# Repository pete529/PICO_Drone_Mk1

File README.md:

# PICO Drone Mk1 – Small Quadcopter 

**Status:** ✅ Hardware design complete and ATO builds are green. BOM is populated (see `hardware/build/builds/default/default.bom.csv`). All hardware has been procured and is ready for PCB assembly.

> **New:** Complete user stories and GitHub issue management system available. See [GitHub Issues Creation](#github-issues-creation) below.

## Overview
This project is a complete Raspberry Pi Pico 2W based quadcopter featuring:
- **Raspberry Pi Pico 2W** module (Wi-Fi enabled RP2040 with wireless connectivity)
- **Dual DRV8833** motor driver ICs (4 independent brushed motor outputs)  
- **GY-91 9-DOF IMU** (ICM-20948 + BMP280 for orientation, acceleration, and altitude)
- **Power management** with LiPo Amigo Pro (boost converter + charging circuit)
- **Status LEDs** (power indicator and user-controllable status)
- **User controls** (power button and mode switching)
- **Robust design** with proper power filtering and protection circuits
- **An Android application** that arms and controls the drone via UDP packets

## Project Structure
```
├── hardware/                    # Main atopile project directory
│   ├── main.ato                # Top-level quadcopter module with complete wiring
│   ├── ato.yaml                # Build configuration with multiple targets
│   ├── atopile/components/     # Custom component definitions
│   ├── layouts/                # KiCad PCB layouts (default + test targets)
│   ├── build/                  # Generated build artifacts
│   └── PART_PICKING_GUIDE.md   # Troubleshooting and part selection guide
├── firmware/                    # Drone firmware & shared protocol utils
│   ├── shared/
│   │   └── control_protocol.py  # CSV parser, deadzone/expo, failsafe smoother
│   └── pico/
│       ├── udp_server.py        # Pico W MicroPython UDP server (AP + UDP control)
│       └── drv8833_stub.py      # DRV8833 test mixer/PWM stub for bring‑up
├── android/                     # Android sender app (Compose)
│   ├── app/src/main/
│   │   ├── AndroidManifest.xml
│   │   └── java/com/petedrone/udpsender/MainActivity.kt
│   ├── app/build.gradle.kts
│   ├── settings.gradle.kts
│   ├── build.gradle.kts
│   └── gradle/wrapper/gradle-wrapper.properties
├── user_stories.md             # Complete user stories (6 epics, 25+ features)
├── create_github_issues.ps1    # Script to create GitHub issues from user stories
├── create_issues.bat           # Windows batch file for easy execution
├── GITHUB_ISSUES_README.md     # Documentation for issue management system
└── .github/workflows/          # CI/CD automation
```

## Current Status

### ✅ **Hardware Design Complete**
- **PCB Design**: Complete atopile design with comprehensive component wiring
- **Build System**: Successfully builds with `ato build` - all stages complete
- **Component Integration**: Pico 2W, dual DRV8833s, GY-91 IMU, power management
- **Signal Routing**: All motor control, I2C, power, and user interface connections
- **Build Artifacts**: KiCad files, BOMs, netlists, and manufacturing files generated

### ✅ **Development Infrastructure**  
- **CI/CD**: Automated builds on every commit with artifact publishing
- **Version Management**: Semantic versioning with automated version bumping
- **Issue Management**: Complete user story system with GitHub issue creation
- **Documentation**: Comprehensive guides for building, troubleshooting, and development

### 🔄 **Next Steps**
- **PCB Assembly**: Assemble the procured components onto the PCB
- **Board Bring-up**: Power-on checks, I²C/UART comms, sensor and motor driver validation
- **Firmware Development**: Flight control algorithms and wireless interface
- **Testing & Validation**: Bench tests and initial flight validation

## Build System

### Local Development
Requirements: Python 3.13+, Atopile 0.12.4

```powershell
# Install atopile (Windows-friendly) - Requires Python 3.13 or later
py -m pip install --upgrade atopile==0.12.4

# From repo root, verify and open the design viewer
ato --version
ato view                    # opens default build (App)

# Build the project (generates KiCad files, BOM, netlist)
ato build

# Build a specific target (pickable resistor demo)
ato build --build test_pickable
```

**Build Output:**
- `build/builds/default/` - Main quadcopter design files
- `build/builds/test_pickable/` - Component testing files
- KiCad PCB files (.kicad_pcb)
- Bill of Materials (.bom.csv) 
- Netlists and component reports

Note: The populated BOM is available at `hardware/build/builds/default/default.bom.csv` after a successful build.

### Troubleshooting Build Issues

**VS Code Extension Error: "Client is not running and can't be stopped"**
- **Cause:** Atopile 0.12.4 requires Python 3.13 or later
- **Solution:** 
  1. Install Python 3.13+ from [python.org](https://www.python.org/downloads/)
  2. Reinstall atopile: `py -m pip install --upgrade atopile==0.12.4`
  3. Restart VS Code
  4. Verify with: `python --version` (should show 3.13.0 or higher)

**Build fails with "No such option: --no-color"**
- **Cause:** Option was added in atopile 0.12.x
- **Solution:** Update to atopile 0.12.4: `pip install --upgrade atopile==0.12.4`

**Version compatibility issues**
- This project requires atopile 0.12.4 specifically due to dependency requirements
- Do not downgrade to 0.2.x versions as they use incompatible syntax and features

## Drone control over Wi‑Fi UDP

This repo includes a MicroPython UDP server for Pico W and an Android sender app.

### Pico W (MicroPython) UDP server

Files:
- `firmware/pico/udp_server.py`
- Shared helpers in `firmware/shared/control_protocol.py`

Behavior:
- Starts Wi‑Fi AP: SSID `PicoDrone`, password `drone1234`
- Listens on UDP port 8888
- Accepts CSV packets at ~50 Hz: `DRN,{throttle},{roll},{pitch},{yaw}\n` (or without `DRN,`)
  - Ranges: throttle [0..1], roll/pitch/yaw [-1..1]
- Optional heartbeat `PING\n` → replies `ACK\n`
- Failsafe: if no valid packet for >500 ms, throttle soft-lands to 0 over 1.5 s

Bring-up steps:
1) Flash MicroPython to Pico W (UF2 from micropython.org).
2) Copy `firmware/` to the board; set `udp_server.py` as main or run from REPL:
	- In Thonny: File → Open `udp_server.py` → Run
3) Observe console: AP IP in `ap.ifconfig()`.

Hooking motors: Replace the TODOs in `udp_server.py` with your motor mixer / ESC driver to apply `(throttle, roll, pitch, yaw)` each loop.

Server configuration (in `udp_server.run_server`):
- `ssid` / `password`: AP SSID/PSK (default `PicoDrone` / `drone1234`)
- `port`: UDP port (default 8888)
- `expect_signature`: set `True` to require the `DRN,` packet prefix
- `deadzone` / `expo`: attitude axis shaping (roll/pitch/yaw)
- PWM test pins: update `mixer.configure_test_pins([2,3,4,5])` to your GPIOs (or remove to print only)

Safety / failsafe:
- Link‑loss (>500 ms) triggers a soft throttle ramp to 0 over ~1.5 s (configurable)
- Always bench‑test with props OFF; verify failsafe before first hover

### Android sender app

Files:
- `android/app/src/main/java/com/petedrone/udpsender/MainActivity.kt`
- `android/app/src/main/AndroidManifest.xml`
- `android/app/build.gradle.kts`

Controls & UX highlights:
- Dual‑joystick Compose controls (left stick: yaw + throttle; right stick: roll + pitch) with deadzone filtering
- Always‑on Material 3 dark theme so labels remain legible in night operations
- Bright yellow drone launcher icon for quick access on the device home screen
- `Armed` toggle that forces throttle to `0` when disabled
- Optional signature prefix toggle (`DRN,`) to satisfy strict firmware configs
- 50 Hz UDP stream with inline `ACK` parsing for battery voltage (`BAT=`) and RSSI telemetry when available

Build & install (Android Studio Hedgehog+ recommended):
1) Open the `android/` folder in Android Studio
2) Let Gradle sync dependencies (Compose + Material3)
3) Run on a connected device; accept prompts if any

Optional (Gradle wrapper, from `android/`):
```powershell
./gradlew assembleDebug   # build APK
./gradlew installDebug    # install to connected device
```

Connect to the Pico:
1) On phone, join the AP `PicoDrone` (password `drone1234`).
2) Open the app; Pico IP is typically `192.168.4.1`, Port `8888`.
3) Toggle Armed and move sliders; the app will emit `DRN,{t},{r},{p},{y}\n` at ~50 Hz.
4) In the Pico console, you should see activity and occasional `ACK` in the app.

📘 **Documentation:** See `docs/mobile_app_user_guide.md` for a complete walkthrough of installation, controls, telemetry, and troubleshooting tips.

Upcoming enhancements to consider next:
- Arming switch latch / stick combination
- In‑app deadzone/expo tuning (server already supports it)
- Packet signature enforcement by default (`expect_signature=True`)
- Simple outbound telemetry from Pico to display battery/RSSI history charts

### Tests

Run parser/failsafe tests locally (CPython):

```powershell
py -m pip install pytest
py -m pytest
```

## Quick Start (end‑to‑end)

1) Build hardware (optional now): `ato build` (see Build System above)
2) Pico W
	- Flash MicroPython UF2
	- Open `firmware/pico/udp_server.py` in Thonny and Run
	- Confirm AP `PicoDrone` is active; note IP (typically `192.168.4.1`)
3) Phone
	- Join `PicoDrone` Wi‑Fi (`drone1234`)
	- Install and open the Android app (from `android/` in Android Studio)
	- Set IP to `192.168.4.1`, Port `8888`, enable `DRN,` if server expects it, Arm ON
	- Move sticks — app sends CSV at ~50 Hz and displays `ACK` on replies
4) On the bench (NO PROPS)
	- Verify throttle response and failsafe (stop app → throttle should ramp to 0)
	- Adjust deadzone/expo if needed

### Automated CI/CD
✅ **GitHub Actions** runs on every push:
- Validates atopile syntax and builds
- Generates all build artifacts
- Publishes downloadable artifacts
- Automated version bumping based on commit messages

**Download artifacts:** Go to any workflow run → Artifacts section

## GitHub Issues Creation

This project includes a comprehensive user story system organized into 6 major epics:

1. **Hardware Design & PCB Development** - Complete hardware platform
2. **Flight Control Software** - Stable and responsive flight control  
3. **Wireless Communication & Control** - Remote piloting capabilities
4. **Development Tools & CI/CD** - Automated build and test systems
5. **Testing & Validation** - Safety and reliability verification
6. **Documentation & User Guide** - Complete instructions and guides

### Creating Issues from User Stories

**Prerequisites:**
- GitHub CLI installed: https://cli.github.com/
- GitHub Personal Access Token: https://github.com/settings/tokens (with `repo` scope)

**Quick Start:**
```powershell
# Windows - Double-click the batch file
create_issues.bat

# Or run PowerShell directly
.\create_github_issues.ps1 -GitHubToken "your_token_here"
```

This will create 25+ GitHub issues organized with labels:
- `epic` - High-level business objectives
- `feature` - Major functional areas  
- `story` - Individual user requirements
- `hardware`, `software`, `testing`, `documentation` - Work categories

**See:** `GITHUB_ISSUES_README.md` for complete documentation

### Issue Automation (Advanced Usage)

The script `create_github_issues.ps1` is **idempotent**: it will not recreate issues that already exist (it checks both open and closed issues by exact title match).

Key features:
- Automatic authentication reuse (you only need `-GitHubToken` if not already logged in with `gh auth login`)
- Full backlog coverage (all epics, features, and stories from `user_stories.md`)
- Label synchronization (missing labels are created on-the-fly)
- Duplicate avoidance (skips existing titles, counts skipped vs created)
- Optional JSON summary output via `-SummaryPath`
- Safe to re-run any time to add only new backlog items

#### Parameters
| Parameter | Required | Description |
|-----------|----------|-------------|
| `-GitHubToken` | No | Personal access token (PAT) with `repo` scope. Optional if already authenticated. |
| `-Owner` | No | Repository owner (default: preset in script) |
| `-Repo` | No | Repository name (default: preset in script) |
| `-SummaryPath` | No | Path to write JSON summary of run (created, skipped, totals) |

#### Examples
```powershell
# 1. First time (no existing gh auth session)
./create_github_issues.ps1 -GitHubToken $env:GITHUB_TOKEN

# 2. Already authenticated via gh
./create_github_issues.ps1

# 3. Capture a summary JSON
./create_github_issues.ps1 -SummaryPath .\issue_summary.json

# 4. Different fork or repo
./create_github_issues.ps1 -Owner YourUser -Repo ForkedRepo -SummaryPath out\summary.json
```

#### Sample Output
```
Checking GitHub authentication...
Verifying repository access (owner/repo)...
Fetching existing issue titles...
Synchronizing labels...
Creating GitHub issues (idempotent)...
↷ Skipping (exists): Epic 1: Hardware Design & PCB Development
✓ Created: Story 2.2.1: Individual Motor Speed Control
...
🚀 Issue creation complete
Created: 57  Skipped: 42  Total Defined: 99  Elapsed: 12.4s
```

#### Summary JSON Schema
```json
{
	"repository": "owner/repo",
	"created": 57,
	"skipped": 42,
	"totalDefined": 99,
	"elapsedSeconds": 12.4,
	"timestamp": "2025-09-23T14:52:31.210Z"
}
```

#### Adding New Stories Later
1. Append new stories to `user_stories.md` using the naming pattern (e.g. `Story 2.4.1:`).
2. Add corresponding hash entry to the `$issues` array in `create_github_issues.ps1`.
3. Re-run the script – only new titles are created; existing ones are skipped.

#### Troubleshooting
| Issue | Cause | Resolution |
|-------|-------|------------|
| Auth error | Not logged in & no token | Run `gh auth login` or pass `-GitHubToken` |
| Label create warnings | Label exists / insufficient perms | Safe to ignore if labels appear in repo |
| Duplicate creation | Title manually changed on GitHub | Align local script title with existing issue |
| >500 existing issues | Pagination limit | (Future) add paging; currently first 500 open + 500 closed |

#### Potential Future Enhancements
- `-DryRun` preview mode
- Filtering (e.g. `-OnlyEpic 3` or `-Match "Motor"`)
- Auto-generated backlog index file
- Changelog-style diff when new stories are added

Open an issue if you need one of these prioritized.

## GitHub Issues Creation (v2 Markdown Parser)

A newer v2 script parses a simple Markdown file and syncs GitHub issues idempotently.

- File format: `# Epic`, `## Feature`, `### Story`
- Optional labels inline: `[labels: a, b]` in the heading, or a `Labels:` line in the body
- Auto adds a type label: `Epic` | `Feature` | `Story`

Usage:

```powershell
# Basic: create missing issues only
./create_github_issues_v2.ps1 -StoriesPath user_stories.md

# Update existing issues (body + labels add). Use -ReplaceLabels to reconcile exactly
./create_github_issues_v2.ps1 -StoriesPath user_stories.md -UpdateExisting
./create_github_issues_v2.ps1 -StoriesPath user_stories.md -UpdateExisting -ReplaceLabels

# Dry run (no changes), plus write summary and markdown report
./create_github_issues_v2.ps1 -StoriesPath user_stories.md -DryRun -SummaryPath issues_summary_v2.json -MarkdownReportPath issues_report_v2.md

# Process a specific chunk (e.g. items 30-44) to avoid long-run hangs
./create_github_issues_v2.ps1 -StoriesPath user_stories.md -UpdateExisting -ReplaceLabels -FromIndex 30 -LimitItems 15 -SummaryPath chunk_30_44.json

# Run all chunks automatically (default size 15)
./run_issue_chunks.ps1 -ChunkSize 15 -UpdateExisting -ReplaceLabels
```

Tips:
- Auth via `gh auth login`, or set `GH_TOKEN` / `GITHUB_TOKEN` env var
- Repo resolution: uses the current repo if `-Owner/-Repo` are not provided
- Labels referenced in Markdown are ensured (created if missing)

### Chunked / Resumable Execution

If very large full runs occasionally stall (external `gh` CLI hang), you can process the backlog in deterministic chunks:

- `-FromIndex N` starts processing at the zero-based index of the parsed markdown items.
- `-LimitItems K` caps how many items are processed in this invocation.
- Together they form a window: `[FromIndex, FromIndex + LimitItems)`.

Helper script `run_issue_chunks.ps1` orchestrates sequential chunks:

```powershell
# Dry run all chunks (no changes)
./run_issue_chunks.ps1 -ChunkSize 20 -DryRun

# Live update with label reconciliation (body+labels) in 15-item windows
./run_issue_chunks.ps1 -ChunkSize 15 -UpdateExisting -ReplaceLabels

# Resume only remaining tail manually
./create_github_issues_v2.ps1 -UpdateExisting -ReplaceLabels -FromIndex 60 -LimitItems 20
```

Each chunk writes its own summary/report (`issues_summary_v2_chunk_#.json`). You can merge results later if desired. This strategy avoids losing progress to a mid-run stall.

### Additional Resilience & Performance Flags (Advanced)

The v2 script also supports advanced flags to make large synchronizations safer and faster:

| Flag | Purpose | Default | When to Use |
|------|---------|---------|-------------|
| `-GhTimeoutSeconds <n>` | Kills and retries any single `gh` CLI call exceeding `n` seconds. | 60 | Full runs that occasionally hang mid-call. |
| `-SkipUnchanged` | Skips body update when the existing GitHub issue body already matches the markdown (still reconciles labels). | Off | Re-running frequent syncs where most stories are unchanged. |

Examples:
```powershell
# Run chunked with a 45s per-call timeout
./run_issue_chunks.ps1 -ChunkSize 15 -UpdateExisting -ReplaceLabels; \
	Get-ChildItem issues_summary_v2_chunk_*.json | Select Name

# Direct window with timeout + skip unchanged bodies
./create_github_issues_v2.ps1 -FromIndex 30 -LimitItems 15 -UpdateExisting -ReplaceLabels -GhTimeoutSeconds 45 -SkipUnchanged

# Speedy dry run sanity check
./create_github_issues_v2.ps1 -DryRun -SkipUnchanged -StoriesPath user_stories.md
```

Effect of `-SkipUnchanged`:
- Performs a lightweight `gh issue view --json body` per issue on update.
- If trimmed body text matches, body update call is omitted, reducing API/process usage.
- Labels are still reconciled (added/removed) respecting `-ReplaceLabels`.

Timeout Behavior (`-GhTimeoutSeconds`):
- Each `gh` invocation is launched in a separate process.
- If it exceeds the timeout, the process is terminated and retried (subject to `-RetryCount` / backoff).
- Exit codes `-999` (timeout) and other non-zero values are treated as transient until retries exhausted.

See `user_stories.template.md` for a sample structure.

## GitHub Issues Creation (v2 REST Variant)

To eliminate occasional external `gh` CLI stalls, a REST-native script `create_github_issues_v2_rest.ps1` provides near feature parity plus extra optimization options.

### Why REST?
| Concern | CLI Variant | REST Variant |
|---------|-------------|--------------|
| External process hangs | Possible on long runs | None (direct HTTP) |
| Per-call timeout | Manual wrapper | Native via `Invoke-RestMethod` timeout |
| Label ensure | Yes | Yes |
| Skip unchanged bodies | String compare | String or hash compare (optional) |
| Hash-based change detection | No | Yes (`-UseBodyHash`) |
| Parse-only mode | Yes (`-ParseOnly` in CLI via earlier improvements) | Yes (`-ParseOnly`) |
| Chunk window | Yes | Yes |
| Replace labels exactly | `-ReplaceLabels` | `-ReplaceLabels` |

### Key Additional Flags
| Flag | Purpose |
|------|---------|
| `-ParseOnly` | Parse markdown and write summaries/reports without any API calls (no token required). |
| `-UseBodyHash` | Appends an HTML comment `<!-- sync-hash:SHA256 -->` to each issue body. Future runs compare only the hash for fast unchanged detection. |
| `-SkipUnchanged` | When used with `-UseBodyHash`, hash comparison avoids fetching or diffing large bodies; otherwise falls back to canonical text compare. |
| `-HttpTimeoutSeconds` | Timeout for each REST call (default 40s) with retries/backoff. |
| `-FilterTitle "regex"` | Process only items whose title matches the supplied case-insensitive regex (applied before chunk window). |

### Usage Examples
```powershell
# 1. Parse-only (no token required) with body hashing to preview generated issues
./create_github_issues_v2_rest.ps1 -ParseOnly -UseBodyHash -StoriesPath user_stories.md -SummaryPath rest_parse.json

# 2. First real creation pass (creates missing issues only)
./create_github_issues_v2_rest.ps1 -GitHubToken $env:GITHUB_TOKEN -UseBodyHash -SummaryPath rest_create.json

# 3. Update existing issues (body + label reconciliation) but skip unchanged using hashes
./create_github_issues_v2_rest.ps1 -UpdateExisting -SkipUnchanged -UseBodyHash -ReplaceLabels -GitHubToken $env:GITHUB_TOKEN -SummaryPath rest_update.json

# 4. Process a specific window (items 30-44) safely
./create_github_issues_v2_rest.ps1 -UpdateExisting -ReplaceLabels -FromIndex 30 -LimitItems 15 -SkipUnchanged -UseBodyHash -GitHubToken $env:GITHUB_TOKEN -SummaryPath rest_chunk_30_44.json

# 5. Pure dry run (no create/update) but still exercise label ensure logic
./create_github_issues_v2_rest.ps1 -DryRun -UpdateExisting -ReplaceLabels -UseBodyHash -SkipUnchanged -GitHubToken $env:GITHUB_TOKEN -SummaryPath rest_dryrun.json

# 6. Only sync WiFi or telemetry related items
./create_github_issues_v2_rest.ps1 -UpdateExisting -ReplaceLabels -FilterTitle "WiFi|Telemetry" -SkipUnchanged -UseBodyHash -GitHubToken $env:GITHUB_TOKEN -SummaryPath rest_wifi.json
```

### Hash Logic Details
- Canonical body removes any existing `<!-- sync-hash:... -->` marker before hashing.
- Hashing uses SHA-256 over UTF-8 bytes of canonical text.
- The hash marker is appended as a final line to persist change fingerprint.
- On `-SkipUnchanged -UseBodyHash`, if existing and new hashes match, body update is skipped (labels still reconciled).

### When to Use Hashing
| Scenario | Recommended? | Benefit |
|----------|--------------|---------|
| Large bodies with frequent re-sync | Yes | Fast equality check, minimal diff noise |
| Many runs with few edits | Yes | Avoids repeated PATCH calls |
| One-off initial import | Optional | Adds marker but no harm |
| Bodies manually edited on GitHub | Caution | Manual edits outside canonical format change hash; script will patch body to restore canonical + marker |

### Summary JSON (REST)
Adds `useBodyHash` boolean to previous schema:
```json
{
	"repository": "owner/repo",
	"dryRun": true,
	"updateExisting": false,
	"replaceLabels": false,
	"useBodyHash": true,
	"createdCount": 0,
	"updatedCount": 0,
	"skippedCount": 0,
	"failedCount": 0,
	"totalFromMarkdown": 71,
	"elapsedSeconds": 0.4
}
```

### Migration Tips
1. Run a `-ParseOnly -UseBodyHash` to preview and inject hashes locally (no API calls).
2. Perform a creation run without `-UpdateExisting` to add any new issues.
3. Follow with `-UpdateExisting -SkipUnchanged -UseBodyHash` for maintenance cycles.
4. Use chunk windows (`-FromIndex/-LimitItems`) only if you anticipate extremely large future backlogs; REST calls are typically stable without chunking.
5. Narrow scope with `-FilterTitle` when iterating on a subset (e.g., `-FilterTitle "^Story 3\\.|WiFi"`).

### Troubleshooting (REST)
| Symptom | Cause | Resolution |
|---------|-------|------------|
| Token error | Missing PAT | Provide `-GitHubToken` or set `GH_TOKEN` / `GITHUB_TOKEN` |
| 403 rate limit | Excessive rapid updates | Add `-ThrottleMs 250` or re-run later |
| Skips expected update | Hash unchanged | Change markdown body or omit `-SkipUnchanged` once |
| Marker visible in UI | Expected | It's a harmless HTML comment; remove `-UseBodyHash` for future runs to stop adding it |

The legacy CLI script remains available; prefer the REST variant for reliability on large sets.

### Merging Multiple Runs

Use `merge_issue_summaries.ps1` to consolidate JSON summaries from both CLI and REST scripts.

```powershell
# Basic merge (auto-glob issues_summary_v2*.json)
./merge_issue_summaries.ps1

# Specify explicit files
./merge_issue_summaries.ps1 -Paths issues_summary_v2_rest_parseonly.json,rest_update_live.json

# Include distinct title lists and write to custom output
./merge_issue_summaries.ps1 -IncludeDetails -Output merged_detailed.json

# Dry run (print to console only)
./merge_issue_summaries.ps1 -DryRun -Glob "rest_*.json"
```

Merged output fields:
- `files`, `totalFiles`
- `repositories` (file count per repo)
- `totals` (created/updated/skipped/failed/defined/filtered)
- `rollup` (net summary)
- `distinctTitles` (only when `-IncludeDetails`)

## Roadmap & Development Status

| Phase | Goal | Status | Issues |
|-------|------|--------|---------|
| ✅ **Phase 1** | Repository + CI/CD infrastructure | **Complete** | Epic 4 |
| ✅ **Phase 2** | Hardware design + component integration | **Complete** | Epic 1 |
| ✅ **Phase 3** | Atopile build system + PCB generation | **Complete** | Epic 1 |
| 🔄 **Phase 4** | Component sourcing + BOM population | **In Progress** | Feature 1.2 |
| 📋 **Phase 5** | Flight control software development | **Planned** | Epic 2 |
| 📋 **Phase 6** | Wireless communication + web interface | **Planned** | Epic 3 |
| 📋 **Phase 7** | Testing + validation + safety systems | **Planned** | Epic 5 |
| 📋 **Phase 8** | Documentation + user guides | **Planned** | Epic 6 |
| 📋 **Phase 9** | PCB manufacturing + assembly | **Future** | Feature 1.3 |
| 📋 **Phase 10** | Flight testing + tuning | **Future** | Epic 2 |

**Current Focus:** Component sourcing and part selection for automated BOM generation

## Technical Specifications

### Hardware
- **Microcontroller:** Raspberry Pi Pico 2W (RP2040 + WiFi)
- **Motor Drivers:** 2x DRV8833 (4 independent brushed DC motor outputs)
- **IMU:** GY-91 (ICM-20948 9-DOF + BMP280 barometer)
- **Power:** LiPo Amigo Pro (boost converter + charging)
- **Connectivity:** WiFi 802.11n, I2C sensors, GPIO controls
- **Indicators:** Status LEDs, user button, power management

### Software (Planned)
- **Flight Control:** PID stabilization loops, sensor fusion
- **Communication:** WiFi AP/STA modes, real-time telemetry
- **Interface:** Web-based control panel, mobile-friendly
- **Safety:** Fail-safe landing, emergency stop, range limiting

## Dual Push (GitHub + GitLab)
Configured by adding GitLab remote earlier. Optional combined push strategy (if desired) can be a script or additional push URL.

To add GitLab as additional push target on `origin` (alternative approach):
```powershell
git remote set-url --add origin https://gitlab.com/pete529/PICO_Drone_Mk1.git
```
(We kept a distinct `gitlab` remote instead to keep fetches clean.)

Push both manually:
```powershell
git push origin main
git push gitlab main
```

## Versioning
We'll start semantic versioning now.
Create a new tag after meaningful milestones:
```powershell
git tag -a v0.1.0 -m "Initial CI + scaffolding"
git push origin v0.1.0
```

An automated workflow (`.github/workflows/bump-version.yml`) inspects commit messages on `main` and will bump the version file (`VERSION`) using these rules:
- `feat:` → minor (unless major bump triggered)
- `BREAKING CHANGE` or `!: ` → major
- otherwise → patch

To disable auto bump for a commit, include `[skip bump]` in the commit message.

## Contributing
Currently private / personal R&D. Future contribution guidelines may include:
- Atopile component style guide
- Pin mapping validation steps
- CI footprint linting

## License
MIT – see `LICENSE`.

## Disclaimer
Electronics provided as-is; verify footprints, clearances, and power integrity before fabrication. Use at your own risk.

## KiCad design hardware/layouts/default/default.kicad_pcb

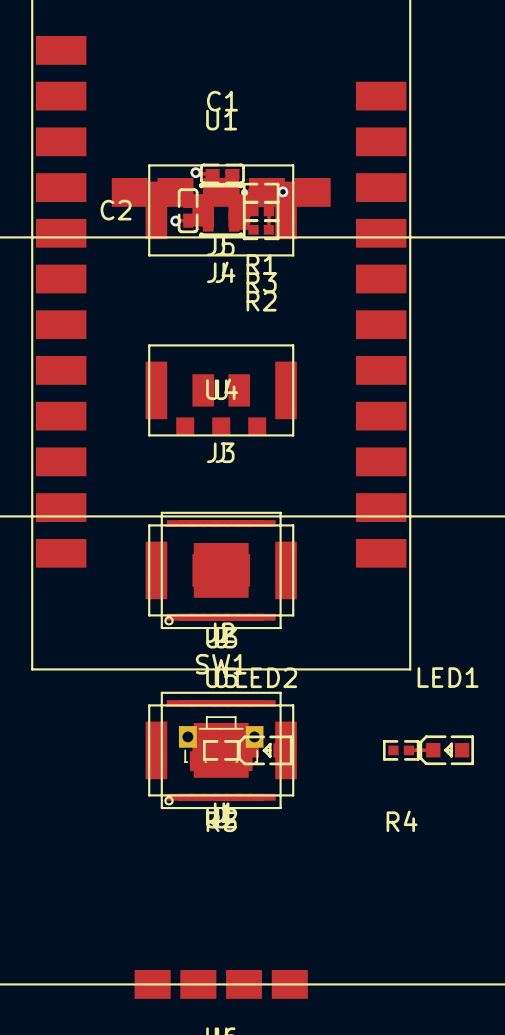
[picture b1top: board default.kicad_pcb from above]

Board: 2 copper layers, 21 parts (0 on the bottom side), 13 nets.

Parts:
C1, C2: 100nF ±10% 16V X7R; C0402
J1, J2, J3, J4: JST_PH_B2B-PH-SM4-TB
J5: AmigoPro_PIM485
LED1, LED2: LED0603-RD
R1, R2, R3, R5: 10kΩ ±1% 62.5mW; R0402
R4: 1kΩ ±1% 62.5mW; R0402
SW1: KEY-SMD_SKTDLDE010
U1: LGA-8_L2.5-W2.0-P0.65_AMP6127
U2, U3: TI_DRV8833
U4: GY-91
U5: Raspberry_Pi_Pico_2W
U6: UBlox_NEO6M

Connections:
CSB: R1.2, U1.2
GND: C1.2, C2.2, J5.GND, R4.2, R5.2, SW1.2, U1.1, U1.7, U2.GND, U3.GND, U4.GND, U5.GND, U6.GND
MOSI: R3.2, U1.3, U4.SDA, U5.SDA
RX: U5.GP0, U6.RX
SCL: R2.2, U1.4, U4.SCL, U5.SCL
TX: U5.GP1, U6.TX
footprint-cathode-0: LED1.1, R4.1
footprint-cathode-1: LED2.1, R5.1
input: SW1.1, U5.GP13
power-anode: LED2.2, U5.GP14
power_3v3-anode: C1.1, C2.1, LED1.2, R1.1, R2.1, R3.1, U1.6, U1.8, U4.VCC, U5.V3V3, U6.VCC
power_5v-VCC: J5.V5, U2.VM, U3.VM
power_batt_out-VCC: J5.VBAT_OUT, U5.VSYS

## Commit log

2025-09-14 change MPU9250 to GP0 & GP1
2025-09-23 Add Atopile quadcopter PCB project structure and initial build system
2025-09-23 chore: add component tasks, release packaging workflow, auto version bump scaffolding
2025-09-23 chore(release): bump version to 0.1.1
2025-09-23 chore(gitignore): expand patterns for envs, releases, caches, keep PCB sources
2025-09-23 chore(release): bump version to 0.1.2
2025-09-23 chore(repo): absorb nested design sub-repos into main repository
2025-09-23 chore(release): bump version to 0.1.3
2025-09-23 refactor(hardware): consolidate to single hardware project and remove legacy duplicates
2025-09-23 chore(release): bump version to 0.1.4
2025-09-23 Fix atopile build issues and complete hardware design
    Resolved all build errors:
    - Fixed missing fp-lib-table files for KiCad footprint resolution
    - Removed invalid footprint assignments causing library errors
    - Created test_pickable build target for part selection validation
    - Added missing component files and proper project structure
    Hardware improvements:
2025-09-23 chore(release): bump version to 0.1.5
2025-09-23 feat: Add comprehensive user stories and GitHub issues management system
    New Features:
    - Complete user stories organized into 6 epics with 25+ features and stories
    - Automated GitHub issues creation from user stories with proper labeling
    - Windows batch script for easy issue creation
    - Comprehensive documentation for issue management workflow
    User Stories Coverage:
2025-09-23 chore(release): bump version to 0.2.0
2025-09-23 feat(issues): full backlog expansion + idempotent creation, label sync, summary output
2025-09-23 chore(release): bump version to 0.3.0
2025-09-23 docs(readme): add advanced issue automation usage section
2025-09-23 chore(release): bump version to 0.4.0
2025-09-23 feat(issues): add v2 markdown parser (create_github_issues_v2.ps1), user stories template, and README usage docs
2025-09-23 feat: issue script batching, resume speed-up, incremental JSON summary & optional markdown report
2025-09-23 chore(gitignore): ignore v2 summary/report artifacts; untrack generated report
2025-09-23 chore(release): bump version to 0.5.0
2025-09-23 chore(gitignore): ignore v2 run artifacts; keep repo clean
2025-09-23 feat(issues): improve v2 parser (bullet story parsing, robust repo/label handling, incremental summary)
2025-09-23 chore(release): bump version to 0.6.0
2025-09-25 feat(issues-sync): add REST variant, hashing optimization, title filtering, merger tool, and docs updates
2025-09-25 chore(release): bump version to 0.7.0
2025-09-26 Firmware: fix FlightComputer syntax, add ComplementaryAHRS, arm button debounce, and UART helper; align wrappers; make tests CPython-friendly (simulation paths)
2025-09-26 chore(release): bump version to 0.8.0
2025-09-26 bmp280_wrapper: guard i2c=None and scan(); allow desktop tests without machine.I2C
2025-09-26 Docs: add arming button, complementary filter, magnetometer support, and desktop test notes to README_firmware.md
2025-09-26 chore(release): bump version to 0.9.0
2025-09-26 Changelog: add 0.8.0 summary; Tooling: add run_tests.py for desktop unittest discovery
2025-09-26 chore(release): bump version to 0.10.0
2025-09-26 test runner: support function-style tests alongside unittest discovery
2025-09-26 CI: add GitHub Actions desktop test workflow; DX: add VS Code test task to run run_tests.py
2025-09-26 chore(release): bump version to 0.11.0
2025-09-26 tests: add unittest-based SensorHub simulation test (desktop-friendly)
2025-09-26 chore(release): bump version to 0.12.0
2025-09-26 tests: add unit tests for PID (integral clamp, limits) and ComplementaryAHRS (static/rate responses)
2025-09-26 chore(release): bump version to 0.13.0
2025-09-26 hardware: add pickable AmigoPro_PIM485 and JST-PH motor connectors; wire into main.ato; update fp-lib-tables; build passes and BOM includes new connectors
2025-09-26 chore(release): bump version to 0.14.0
2025-09-26 chore(parts): add supplier metadata for AmigoPro (PIM485), Aideepen GPS (Amazon ASIN B08CZSL193), and GY-91; build verified. note: picker doesnt support these suppliers yet. also prep AmigoPro for ex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
2025-09-26 chore(release): bump version to 0.15.0
2025-09-26 ci: fix artifact paths for Atopile outputs; add diagnostics and logs upload; correct release workflow to use hardware/ and dist paths
2025-09-26 chore(release): bump version to 0.16.0
2025-09-26 feat(amigopro): update PIM485 footprint to 35x23mm, set pad row 2.5mm from top; add drawing link and fab notes; rebuild ok
2025-09-26 chore(release): bump version to 0.17.0
2025-09-26 ci(release): add diagnostics and robust artifact path handling; ci(build): allow BOM/artifacts from hardware/ or root build outputs; chore(hardware): include modules path in hardware/ato.yaml
2025-09-26 chore(release): bump version to 0.18.0
2025-09-26 ci(build): collect outputs into dist/builds/default and upload from there; expand diagnostics and BOM detection for robustness
2025-09-26 chore(release): bump version to 0.19.0
2025-10-05 test: add unittest shim to wrap function-style tests so python -m unittest discover runs full suite
2025-10-05 chore(release): bump version to 0.20.0
2025-10-05 drivers(icm20948): add minimal ICM-20948 driver; sensors(imu): prefer ICM-20948 with graceful fallback; tests: add ICM-20948 basic test and keep unittest discovery via shim
2025-10-05 chore(release): bump version to 0.21.0
2025-10-05 gps(neo6m): add minimal NMEA parser and UART helper; sensors: add GPS wrapper and integrate into SensorHub; tests: add RMC/GGA parsing test; unittest discovery runs full suite
2025-10-05 chore(release): bump version to 0.22.0
2025-10-05 hardware(gps): switch to u-blox NEO-6M logical part, update symbol metadata, and wire new module in main.ato; build verified
2025-10-05 chore(release): bump version to 0.23.0
2025-10-05 hardware(gps/cad): rename Aideepen CAD libs to UBlox_NEO6M (symbol+footprint), update fp-lib-tables, and switch main.ato to UBlox_NEO6M; ato build OK
2025-10-05 chore(release): bump version to 0.24.0
2025-10-06 hardware/main.ato: cleanup unused nets; direct instance wiring; add UBlox NEO-6M GPS with UART0 and power; wire drv_right.SLEEP; reduce duplicate net names
2025-10-06 chore(release): bump version to 0.25.0
2025-10-06 chore: clear remaining warnings\n- packages/bosch-bmp280/ato.yaml: valid identifier and author email\n- parts/UBlox_NEO6M: add has_part_picked (lcsc)\n- parts/AmigoPro_PIM485: add has_part_picked (lc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
2025-10-06 chore(release): bump version to 0.26.0
2025-10-06 fix(hardware): correct GPS pin names and component references; clean header/comments; restore supported imports
2025-10-06 chore(release): bump version to 0.27.0
2025-10-06 docs: update project status to reflect populated BOM and hardware procured; add BOM path reference
2025-10-06 chore(release): bump version to 0.28.0
2025-10-06 feat(control): Pico UDP server + DRV8833 driver wiring from hardware pins; telemetry ACK; failsafe\nfeat(android): dual-joystick JetStick UI with telemetry parsing; Gradle wrapper\nchore(tests): Rasp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
2025-10-06 chore(release): bump version to 0.29.0
2025-10-08 Complete Android app build setup and customization
    - Upgrade Kotlin to 1.9.24 for Compose compatibility
    - Fix JetStick.kt compilation errors (scope resolution, type ambiguity)
    - Add Android Gradle configuration (gradle.properties, local.properties)
    - Include Gradle wrapper for consistent builds
    - Customize app name to 'Pete Drone ctrler'
    - Adjust joystick layout for right-side alignment
2025-10-08 chore(release): bump version to 0.30.0
2025-10-08 fix: Add Android build artifacts to .gitignore
    - Exclude android/.gradle/ directory from version control
    - Exclude android build directories and APK/AAB files
    - Prevent accidental staging of Gradle cache files
    This resolves the issue where 16 Gradle build artifacts were
    accidentally staged for commit.
2025-10-08 chore(release): bump version to 0.31.0
2025-10-08 feat: Add dark mode theme and custom drone icon
    - Enable dark mode theme for better visibility in low light
    - Create custom yellow drone icon on black background
    - Add vector drawable app icons (adaptive icon support)
    - Port 8888 already configured as default
    - Improve text contrast for dark mode usage
    The app now displays properly in dark mode and features
2025-10-08 feat: Add custom yellow drone app icon
    - Create vector drawable drone icon with yellow color on black background
    - Add adaptive icon support for modern Android versions
    - Include both standard and round icon variants
    - Professional drone silhouette design for app identification
2025-10-08 chore(release): bump version to 0.32.0
2025-10-08 docs: add android user guide and expand tests
2025-10-08 chore(release): bump version to 0.33.0
2025-10-08 android: refresh dark mode labels and icon
2025-10-08 chore(release): bump version to 0.34.0
2025-10-09 Replace launcher icon with provided PNG
2025-10-09 updated andriod images, improved security on wifi credentials and added new mobile app to server test rig
2025-10-09 Refresh Gradle wrapper to 8.7
2025-10-09 feat: add launcher icon generator and updated icons
2025-10-09 chore: remove obsolete KiCad files and update firmware/hardware
2025-10-09 chore(release): bump version to 0.35.0
2025-11-13 Initial plan
2025-11-13 Fix atopile client connection error by updating Python version requirement to 3.13
2025-11-13 Add troubleshooting section for Python version and VS Code extension issues
2025-11-13 Update GPIO pin assignments for DRV8833 motor drivers to GP2-5 and GP6-9
2025-11-13 Add comprehensive GPIO documentation and comparison tables
2025-11-13 Add implementation ready guide for hardware assembly
2025-11-13 Fix critical syntax errors and rename functions to use approved PowerShell verbs
2025-11-13 Fix Ato paths, DRV8833 pinmap, Pico I2C/GPIO, and LED module
2025-11-13 add new tests and improve wifi security
2025-11-13 Apply Android build fixes and compose UI
2025-11-13 chore(release): bump version to 0.36.0
2025-11-13 Update docs and add motor/BMP tests
2025-11-13 chore(release): bump version to 0.37.0
2025-11-13 chore(release): bump version to 0.38.0
2025-11-19 chore(release): bump version to 0.39.0
